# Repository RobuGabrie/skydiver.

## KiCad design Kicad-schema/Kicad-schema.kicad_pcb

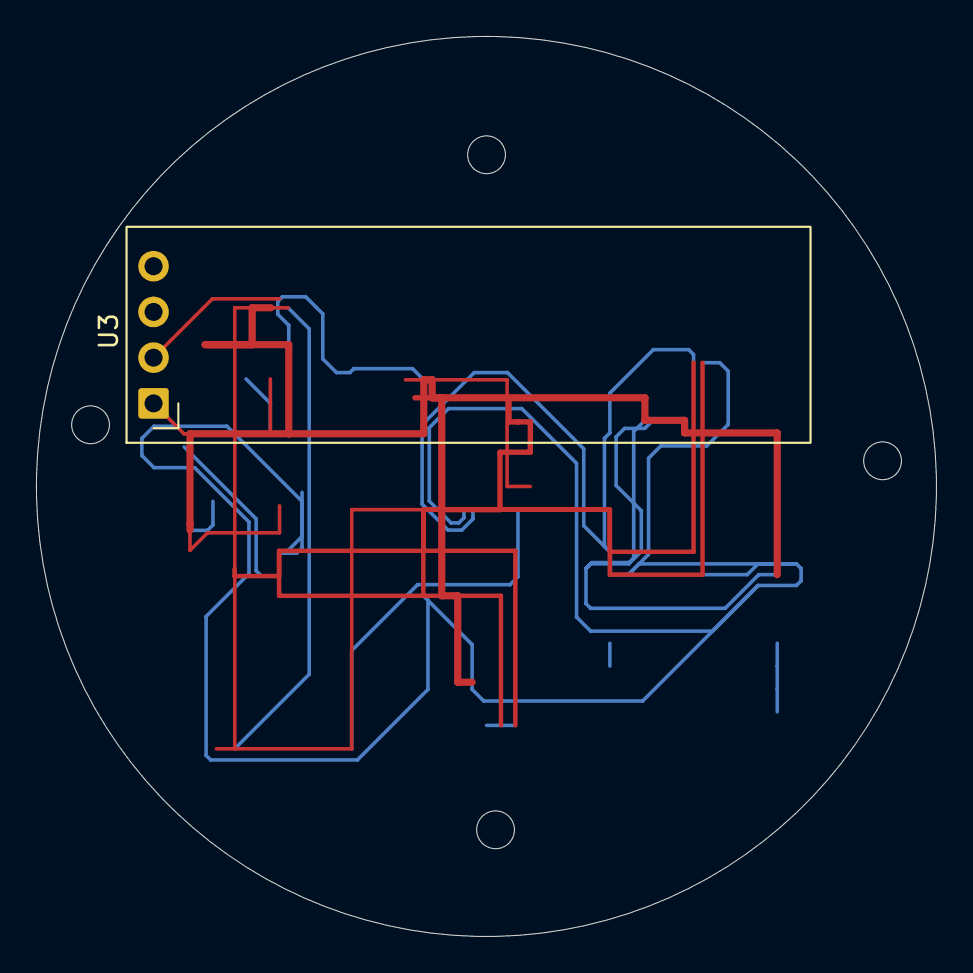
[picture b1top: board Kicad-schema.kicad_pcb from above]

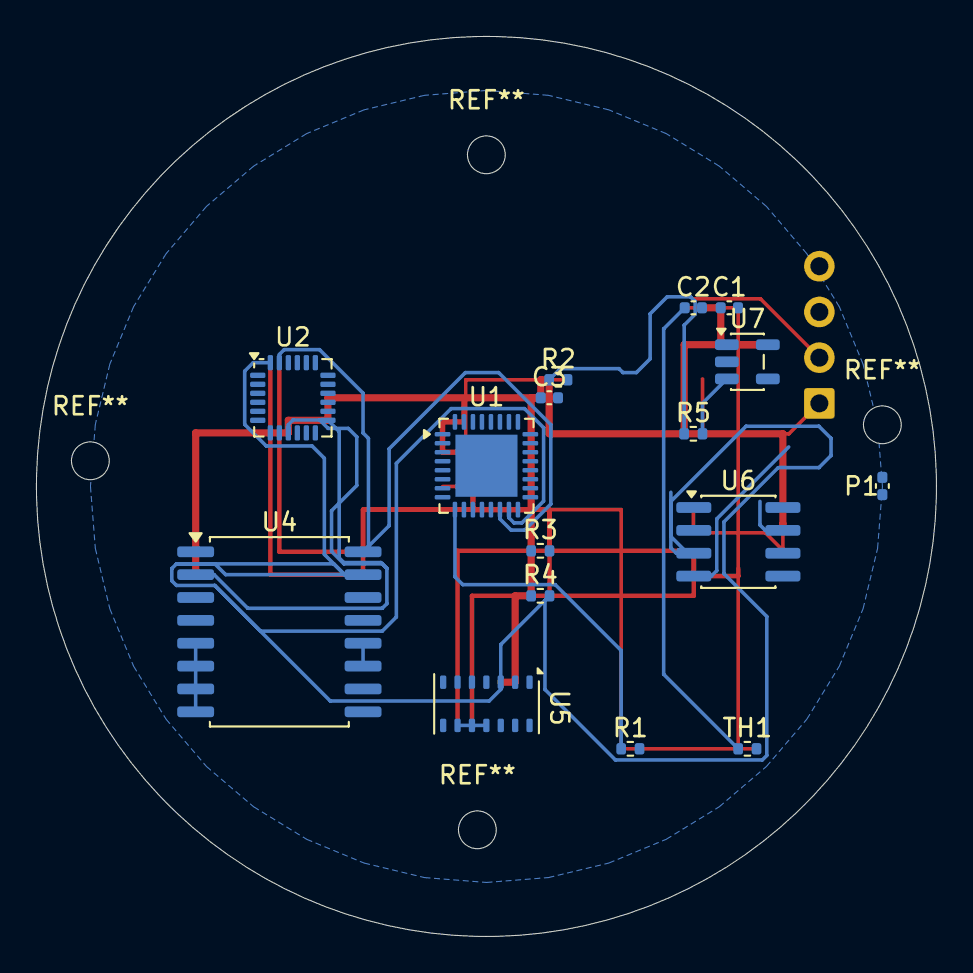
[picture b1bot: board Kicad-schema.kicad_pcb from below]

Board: 4 copper layers, 50.0 x 50.0 mm, 17 parts (16 on the bottom side), 9 nets.

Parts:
C1: 100nf; C_0402_1005Metric
C2: 10uf; C_0402_1005Metric
C3: 100nF; C_0402_1005Metric
P1: USB_C_Plug_USB2.0; C_0402_1005Metric
R1, R2, R5: 10kohm; R_0402_1005Metric
R3, R4: 4.7kohm; R_0402_1005Metric
TH1: Thermistor_NTC; R_0402_1005Metric
U1: ESP32-C3; QFN-32-1EP_5x5mm_P0.5mm_EP3.45x3.45mm
U2: MPU-6050; InvenSense_QFN-24_4x4mm_P0.5mm
U3: ER_OLEDM0.91_1x-I2C
U4: DS3231M; SOIC-16W_7.5x10.3mm_P1.27mm
U5: MAX30102; Maxim_OLGA-14_3.3x5.6mm_P0.8mm
U6: INA219AxD; SOIC-8_3.9x4.9mm_P1.27mm
U7: AP2112K-3.3; SOT-23-5

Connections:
GND: C1.2, R1.2, U1.33 (GND), U2.1 (CLKIN), U2.18 (GND), U3.1 (GND), U4.5 (GND), U4.6 (GND), U4.7 (GND), U4.8 (GND), U4.9 (GND), U4.10 (GND), U4.11 (GND), U4.12 (GND), U4.13 (GND), U5.4 (PGND), U5.12 (GND), U6.1 (A1), U6.2 (A0), U6.6 (GND), U7.2 (GND)
unnamed: C2.1, TH1.1
unnamed: R2.2, U1.1 (LNA_IN), U1.7 (CHIP_EN)
unnamed: R3.2, U1.14 (GPIO8), U2.23 (SCL), U3.3 (SCL), U4.16 (SCL), U5.2 (SCL), U6.4 (SCL)
unnamed: R4.2, U1.15 (GPIO9/BOOT), U2.24 (SDA), U3.4 (SDA), U4.15 (SDA), U5.3 (SDA), U6.3 (SDA)
unnamed: R1.1, TH1.2, U1.9 (MTMS/GPIO4/ADC1_CH4)
unnamed: C3.2, U1.2 (VDD3P3), U1.3 (VDD3P3), U1.11 (VDD3P3_RTC), U1.17 (VDD3P3_CPU), U1.31 (VDDA), U1.32 (VDDA)
unnamed: C1.1, C2.2, C3.1, R2.1, R3.1, R4.1, R5.1, U2.9 (AD0), U2.13 (VDD), U3.2 (VCC), U4.2 (VCC), U5.9 (VLED+), U5.10 (VLED+), U5.11 (VDD), U6.7 (IN-), U7.5 (VOUT)
unnamed: R5.2, U7.3 (EN)

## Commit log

2026-04-22 Track web as regular directory
2026-04-22 Fix React 19.1.0 version and sync lock file
2026-04-23 designed mobile app
2026-04-23 Fix React version 19.1.0 and update lock file
2026-04-28 finished app
